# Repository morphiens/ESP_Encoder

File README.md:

# ESP Encoder

A collection of ESP32-based encoder measurement projects using the AS5047D 14-bit magnetic rotary encoder.

Each project lives in `projects/` with its own Python scripts. All projects share firmware templates from `firmware/`.

---

## Firmware Templates

| Template | Location | Use When |
|---|---|---|
| **Single Encoder** | [`firmware/single_encoder/`](firmware/single_encoder/) | One ESP reads one encoder, sends directly to PC via BLE |
| **Dual Encoder** | [`firmware/dual_encoder/`](firmware/dual_encoder/) | One ESP reads two encoders on same SPI bus, sends to PC via BLE |
| **Master** | [`firmware/master/`](firmware/master/) | ESP32C6 — aggregates encoder data from slaves, sends to PC via BLE |
| **Slave** | [`firmware/slave/`](firmware/slave/) | ESP32C3 — reads one encoder, responds to master over ESP-NOW |

### Flashing a Single-Encoder Project

1. Open `firmware/single_encoder/single_encoder.ino` in Arduino IDE
2. Edit the config block at the top:
   ```cpp
   #define ESP_NAME            "YOUR_DEVICE_NAME"
   #define SERVICE_UUID        "4fafc201-..."
   #define CHARACTERISTIC_UUID "beb5483e-..."
   ```
3. Select board (XIAO ESP32C3 or ESP32C6) and upload

### Flashing a Multi-Encoder Project (Master + Slave)

See [`Oliver/README.md`](Oliver/README.md) for full setup instructions.

---

## Projects

| Project | Firmware | Description |
|---|---|---|
| [block_height](projects/block_height/) | Single Encoder | Block height from encoder rotation via trigonometry or polynomial fit |
| [Oliver](Oliver/) | Master + Slave | Wireless multi-encoder system (ESP32C6 master + ESP32C3 slaves) |

---

## Repository Structure

```
Esp_Encoder/
├── firmware/
│   ├── single_encoder/
│   │   └── single_encoder.ino    # Single ESP → BLE to PC
│   ├── dual_encoder/
│   │   └── dual_encoder.ino      # Single ESP reading 2 Encoders → BLE to PC
│   ├── master/
│   │   └── master.ino            # ESP32C6 master — aggregates slaves, sends BLE
│   └── slave/
│       └── slave.ino             # ESP32C3 slave — reads encoder, replies via ESP-NOW
│
├── projects/
│   └── block_height/             # Block height measurement Python scripts
│
├── Oliver/                       # Multi-encoder project (firmware + Python)
│   ├── master/master.ino         # (copy of firmware/master)
│   ├── slave/slave.ino           # (copy of firmware/slave)
│   ├── oliver.py                 # Python API for BLE communication
│   ├── oliver_raw.py             # Raw BLE data script
│   └── README.md
│
├── Datasheets/
│   └── AS5047D.pdf
├── requirements.txt
├── setup.sh
└── README.md
```

---

## How It Works

### Ultra-Precision Sampling Algorithm

All projects use the same AS5047D reading algorithm:

1. **4,096 raw SPI reads**, split into 16 blocks of 256 samples
2. **Robust mean per block** — discard samples > 1.5 LSB from mean, re-average the rest
3. **Median of 16 block means** — rejects any block corrupted by radio bursts
4. **Convert to degrees**: `angle = (counts × 360) / 16384`

### Single-Encoder BLE Data Format

The single encoder uses the **same 7-field format as Oliver master** for protocol compatibility:

```
<packetIdx>|M0:<angle>,<pkt>,<agc>,<mag>,<magl>,<magh>,<cof>
```

Example: `5|M0:1669900,5,38,1823,0,0,0`

| Field | Description |
|---|---|
| `packetIdx` | Global packet counter (increments per READ) |
| `angle` | Encoder angle × 10000 as integer (e.g. `1669900` = 166.9900°) |
| `pkt` | Same as packetIdx (per-encoder index) |
| `agc` | Automatic gain control (0–255) |
| `mag` | CORDIC magnitude (field strength) |
| `magl / magh / cof` | Diagnostic flags (0 or 1) |

**BLE Commands:**

| Command | Description |
|---|---|
| `READ` | Request one on-demand encoder reading |
| `ZERO` | Set current position as zero reference |

### Multi-Encoder (Oliver) BLE Data Format

```
<gateway_idx>|M0:<angle>,<pkt>,<agc>,<mag>,<magl>,<magh>,<cof>|S0:...|S1:...
```

See [`Oliver/README.md`](Oliver/README.md) for full protocol details.

---

## Getting Started

```bash
./setup.sh
source .venv/bin/activate
```

## License

MIT

---

**Author:** Swaraj Dangare

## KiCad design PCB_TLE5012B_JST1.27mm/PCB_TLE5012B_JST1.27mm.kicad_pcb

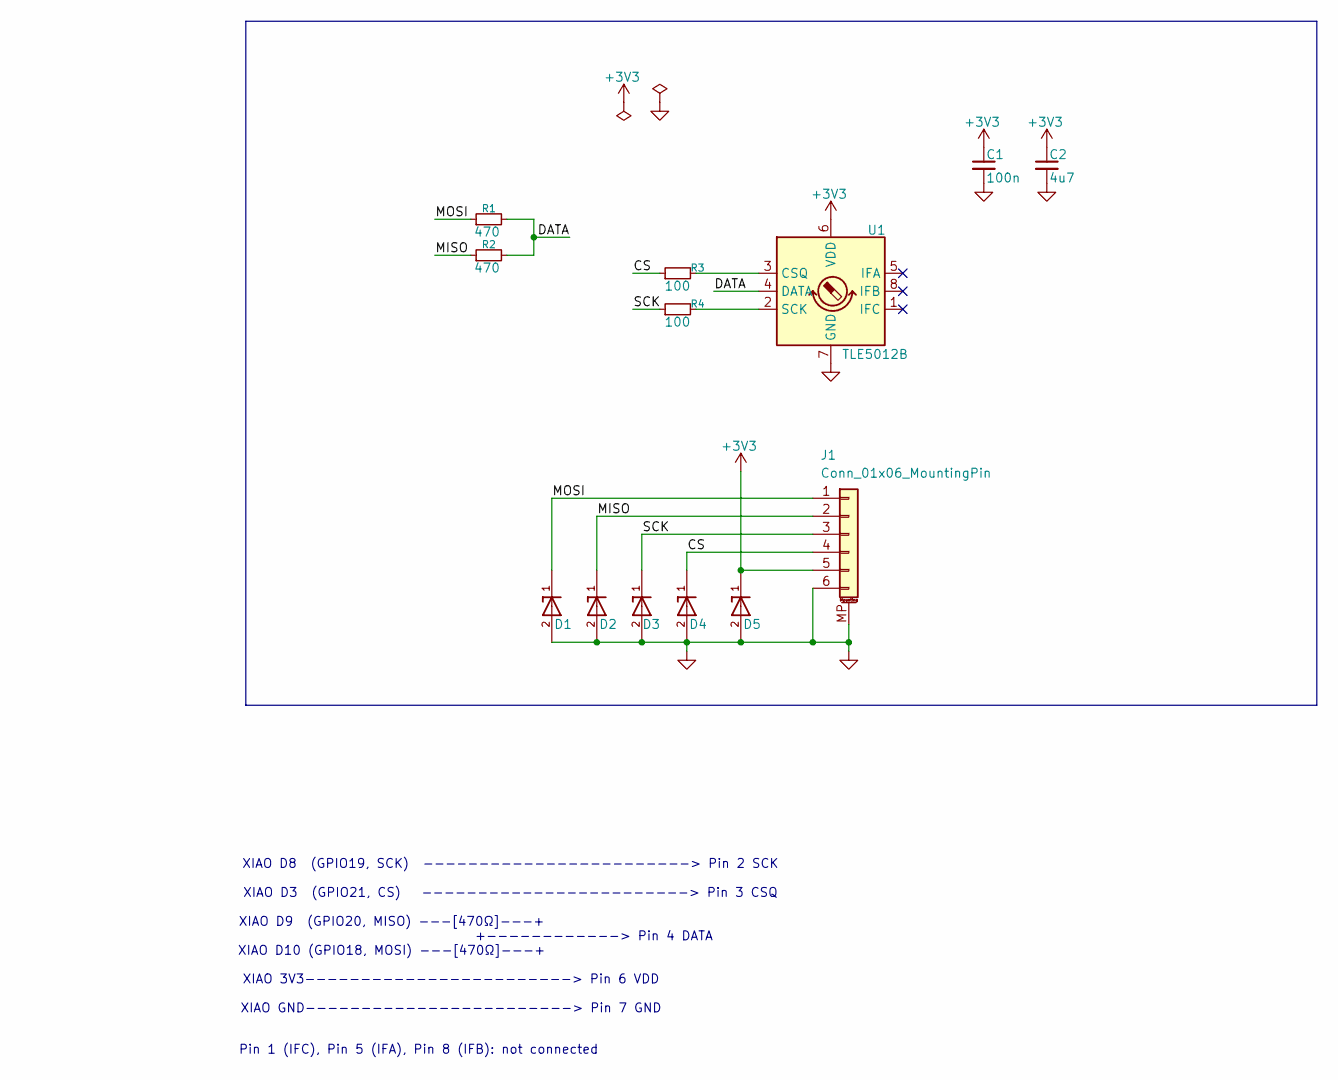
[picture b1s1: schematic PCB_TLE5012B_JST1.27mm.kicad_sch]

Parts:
C1: 100n; C_0603_1608Metric_Pad1.08x0.95mm_HandSolder
C2: 4u7; C_0603_1608Metric_Pad1.08x0.95mm_HandSolder
D1, D2, D3, D4: TPD1E05U06DPYR; D_SOD-523; PARTREV B
D5: TPD1E05U06DPYR; D_SMF; PARTREV B
J1: Conn_01x06_MountingPin; JST_SH_SM06B-SRSS-TB_1x06-1MP_P1.00mm_Horizontal
R1, R2: 470; R_0603_1608Metric_Pad0.98x0.95mm_HandSolder
R3, R4: 100; R_0603_1608Metric_Pad0.98x0.95mm_HandSolder
U1: TLE5012B; SOIC-8_3.9x4.9mm_P1.27mm

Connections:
+3V3: C1.1, C2.1, D5.1, J1.5, U1.6 (VDD)
/CS: D4.1, J1.4, R3.1
/DATA: R1.2, R2.2, U1.4 (DATA)
/MISO: D2.1, J1.2, R2.1
/MOSI: D1.1, J1.1, R1.1
/SCK: D3.1, J1.3, R4.1
GND: C1.2, C2.2, D1.2, D2.2, D3.2, D4.2, D5.2, J1.6, J1.MP (MountPin), U1.7 (GND)
unnamed: R3.2, U1.3 (CSQ)
unnamed: R4.2, U1.2 (SCK)

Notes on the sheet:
XIAO D9 (GPIO20, MISO) ---[470Ω]---+ +------------> Pin 4 DATA XIAO D10 (GPIO18, MOSI) ---[470Ω]---+
XIAO 3V3------------------------> Pin 6 VDD XIAO GND------------------------> Pin 7 GND
Pin 1 (IFC), Pin 5 (IFA), Pin 8 (IFB): not connected
XIAO D8 (GPIO19, SCK) ------------------------> Pin 2 SCK XIAO D3 (GPIO21, CS) ------------------------> Pin 3 CSQ

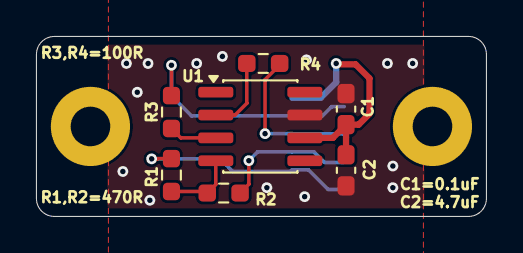
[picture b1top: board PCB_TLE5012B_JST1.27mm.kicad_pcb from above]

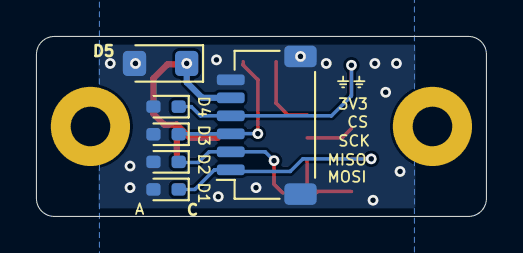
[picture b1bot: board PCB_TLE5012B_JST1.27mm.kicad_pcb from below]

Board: 2 copper layers, 25.0 x 10.0 mm, 15 parts (6 on the bottom side), 9 nets.

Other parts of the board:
H1, H2: MountingHole; MountingHole_2.2mm_M2_Pad

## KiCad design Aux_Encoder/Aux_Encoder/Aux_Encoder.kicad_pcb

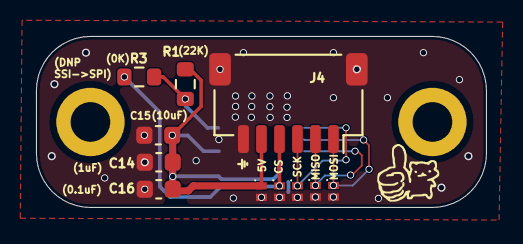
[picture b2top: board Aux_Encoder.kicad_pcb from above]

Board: 2 copper layers, 25.0 x 9.5 mm, 14 parts (1 on the bottom side), 7 nets.

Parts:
C14: 100nF; C_0603_1608Metric
C15: 10uF; C_0603_1608Metric
C16: 1uF; C_0603_1608Metric
D11: ESD321DPYR; TPD1E05U06DPYR
D12, D13, D14, D15: TPD1E05U06DPYR
H1, H2: MountingHole; MountingHole_2.2mm_M2_DIN965_Pad
J4: Conn_01x06_MountingPin; JST_SH_SM06B-SRSS-TB_1x06-1MP_P1.00mm_Horizontal
R1: 22K; R_0603_1608Metric
R3: 0K; R_0603_1608Metric
U1: AEAT-8800-Q24; IC_AEAT-8800-Q24

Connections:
+3.3V: C14.1, C15.1, C16.1, D15.1, J4.5, R1.1, U1.14 (VDDA), U1.19 (VDDA)
/CS: D14.1, J4.4, R3.1
/MISO: D12.1, J4.2, U1.12 (SSI_DO_SPI_DO)
/MOSI: D11.1, J4.1, U1.11 (SSI_NSL_SPI_DI)
/SCK: D13.1, J4.3, U1.10 (SSI_SCL_SPI_CLK)
GND: C14.2, C15.2, C16.2, D11.2, D12.2, D13.2, D14.2, D15.2, J4.6, J4.MP (MountPin), U1.13 (VSS), U1.20 (VSS), U1.25 (VSS)
unnamed: R1.2, R3.2, U1.21 (SSI_SPI_SEL)

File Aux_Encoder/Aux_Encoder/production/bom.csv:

Designator,Footprint,Quantity,Value,LCSC Part #
C14,0603,1,100nF,
C15,0603,1,10uF,
C16,0603,1,1uF,
D11,TPD1E05U06DPYR,1,ESD321DPYR,C436349
"D12, D13, D14, D15",TPD1E05U06DPYR,4,TPD1E05U06DPYR,C436349
J4,JST_SH_SM06B-SRSS-TB_1x06-1MP_P1.00mm_Horizontal,1,Conn_01x06_MountingPin,
R1,0603,1,22K,
R3,0603,1,0K,
U1,IC_AEAT-8800-Q24,1,AEAT-8800-Q24,

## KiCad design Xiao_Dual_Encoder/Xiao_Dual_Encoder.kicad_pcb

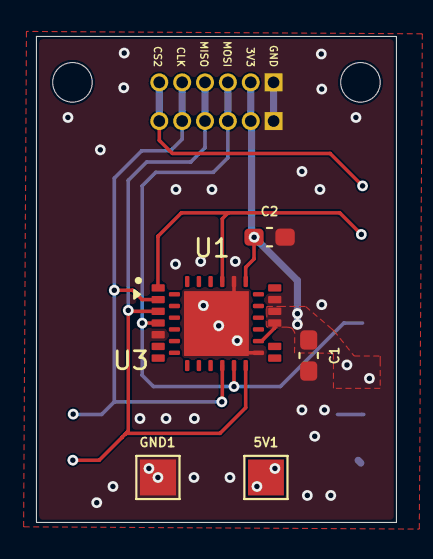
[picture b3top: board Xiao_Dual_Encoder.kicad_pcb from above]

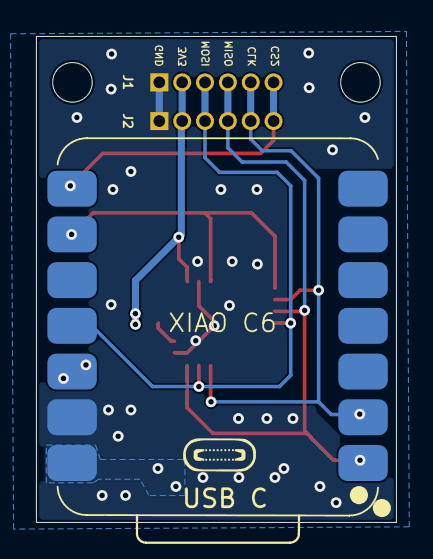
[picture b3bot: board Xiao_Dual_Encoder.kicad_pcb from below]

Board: 2 copper layers, 20.0 x 27.0 mm, 9 parts (3 on the bottom side), 8 nets.

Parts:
5V1: TestPoint; TestPoint_Pad_2.0x2.0mm
C1, C2: 100n; C_0603_1608Metric_Pad1.08x0.95mm_HandSolder
GND1: TestPoint; TestPoint_Pad_2.0x2.0mm
J1, J2: Conn_01x06_Pin; PinHeader_1x06_P1.27mm_Vertical
U1: AEAT-8800-Q24; QFN-24-1EP_5x5mm_P0.65mm_EP3.6x3.6mm
U2: Xiao C6; Xiao_C6_SMD
U3: AS5047P-ATSM; SOP65P640X120-14N

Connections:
+3.3V: C1.1, C2.1, J1.2, J2.2, U1.14 (VDDA), U1.19 (VDDA), U2.12 (3V3), U3.11 (VDD), U3.12 (VDD3V3)
CLK: J1.5, J2.5, U1.10 (SSI_SCL_SPI_CLK), U2.2 (D1/A1), U3.2 (CLK)
CS1: U1.21 (SSI_SPI_SEL), U2.9 (D8/SCK), U3.1 (CSN)
CS2: J1.6, J2.6, U2.8 (RX/D7)
GND: C1.2, C2.2, GND1.1 (1_1), J1.1, J2.1, U1.13 (VSS), U1.20 (VSS), U1.25 (VSS), U2.13 (GND), U3.5 (TEST), U3.13 (GND)
MISO: J1.4, J2.4, U1.12 (SSI_DO_SPI_DO), U2.1 (DO/A0/Interrupt0), U3.3 (MISO)
MOSI: J1.3, J2.3, U1.11 (SSI_NSL_SPI_DI), U2.11 (D10/MOSI), U3.4 (MOSI)
unnamed: 5V1.1 (1_1), U2.14 (VBUS)

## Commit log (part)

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2026-02-16 Add README.md for Oliver project detailing architecture, hardware, setup, and usage instructions
2026-02-16 Add on-demand reading functionality to the Oliver project, enhancing encoder data retrieval. Updated README.md with detailed on-demand data flow and encoder angle calculation. Added .venv to .gitigno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
2026-02-18 added Oliver 3
2026-02-19 feat: align single_encoder protocol with Oliver master
    firmware/single_encoder/single_encoder.ino:
    - Switch from continuous to on-demand trigger (PC writes "READ" to fire a reading)
    - Rename zero command: "Z" → "ZERO"
    - Change angle representation: float string → integer × 10000
    - Add global packetIdx counter (increments on each READ)
    - Adopt Oliver-compatible pipe-delimited BLE message format:
2026-04-16 [Swaraj] add BLE firmware for dual AS5047D magnetic encoders on ESP32
2026-04-16 [Swaraj] added readme for dual encoder.ino
2026-05-17 [Swaraj]Add unified firmware for XIAO ESP32-C6 in the Oliver cluster. Introduced BLE setup mode, runtime modes (master, slave, standalone), and ESP-NOW communication. Added README.md with detailed in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
2026-05-18 [Swaraj ]Add AEAT-8800-Q24 magnetic encoder firmware and documentation
    - Introduced new firmware for the AEAT-8800-Q24 16-bit absolute magnetic rotary encoder, supporting both SSI and SPI protocols.
    - Added detailed pin mapping, SSI read sequence, and SPI protocol specifications in the code comments.
    - Included a comprehensive data sheet for the AEAT-8800-Q24 in PDF format, outlining key features, specifications, and applications.
2026-05-21 Update CS and SPI pin assignments for encoders
2026-05-27 [Krishna] 14 bit encoder test
2026-06-09 [Swaraj] Refactor encoder pin definitions and add dual encoder firmware
